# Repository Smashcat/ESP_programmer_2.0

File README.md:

# ESP_programmer_2.0
A USB to serial device plus circuit to automatically put ESP8266 and ESP32 modules into programming mode when programming via Arduino. Board is based around the CP2104 USB to serial bridge. All parts surface mount, except for header pins - project created using Eagle.

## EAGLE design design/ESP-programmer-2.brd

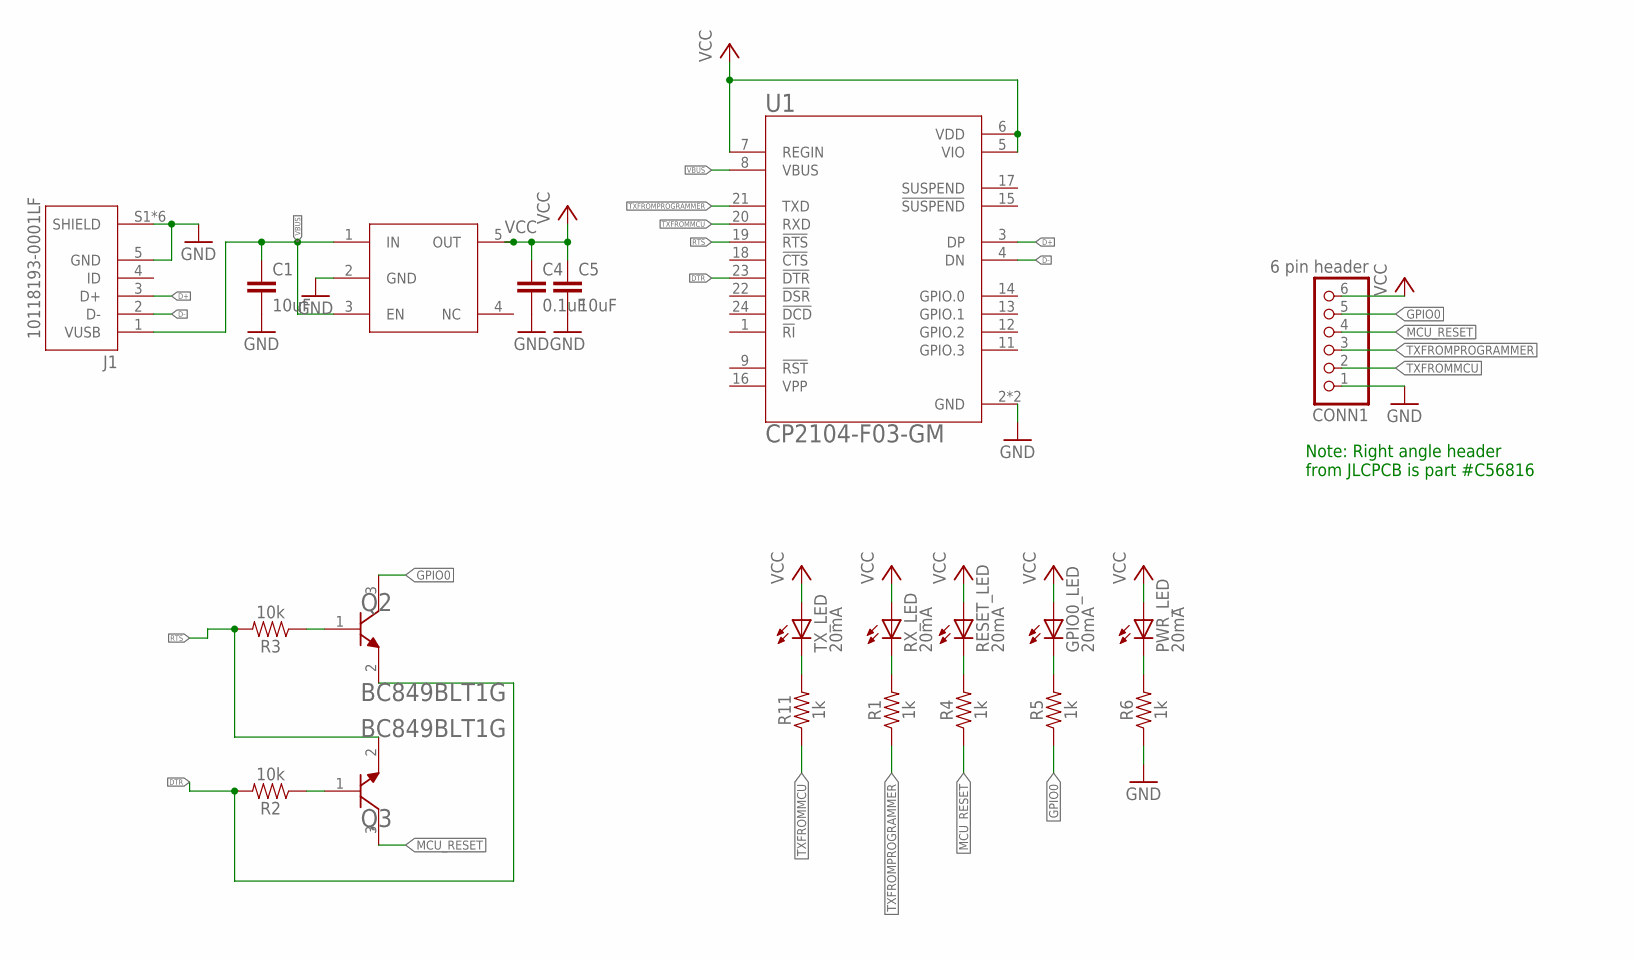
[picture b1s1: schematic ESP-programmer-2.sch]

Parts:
C1, C5: 10uF; C0603
C4: 0.1uF; C0603
CONN1: 6 pin header; 1X06
GPIO0_LED: 20mA; CHIP-LED0603
J1: 10118193-0001LF; FCI_10118193-0001LF
PWR_LED: 20mA; CHIP-LED0603
Q2, Q3: ON_SEMICONDUCTOR_BC849BLT1GON_SEMICONDUCTOR_BC849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; ON_SEMICONDUCTOR_BC849BLT1G_0
R1, R4, R5, R6, R11: 1k; 0603
R2, R3: 10k; 0603
REG: 3v3 LDO; NCP718BSN330T1G
RESET_LED: 20mA; CHIP-LED0603
RX_LED: 20mA; CHIP-LED0603
TX_LED: 20mA; CHIP-LED0603
U1: CP2104-F03-GM; QFN50P400X400X80-25N

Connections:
D+: J1.3 (D+), U1.3 (DP)
D-: J1.2 (D-), U1.4 (DN)
DTR: Q2.2 (E), R2.2, U1.23 (!DTR)
GND: C1.2, C4.2, C5.2, CONN1.1, J1.5 (GND), J1.S1 (SHIELD), J1.S2 (SHIELD), J1.S3 (SHIELD), J1.S4 (SHIELD), J1.S5 (SHIELD), J1.S6 (SHIELD), R6.1, REG.2 (GND), U1.2 (GND), U1.25 (GND)
GPIO0: CONN1.5, Q2.3 (C), R5.1
MCU_RESET: CONN1.4, Q3.3 (C), R4.1
unnamed: Q3.1 (B), R2.1
unnamed: Q2.1 (B), R3.1
RTS: Q3.2 (E), R3.2, U1.19 (!RTS)
STATUSTOLED: R11.2, TX_LED.C
STATUSTOLED1: R1.2, RX_LED.C
STATUSTOLED2: R4.2, RESET_LED.C
STATUSTOLED3: GPIO0_LED.C, R5.2
STATUSTOLED4: PWR_LED.C, R6.2
TXFROMMCU: CONN1.2, R11.1, U1.20 (RXD)
TXFROMPROGRAMMER: CONN1.3, R1.1, U1.21 (TXD)
VBUS: C1.1, J1.1 (VUSB), REG.1 (IN), REG.3 (EN), U1.8 (VBUS)
VCC: C4.1, C5.1, CONN1.6, GPIO0_LED.A, PWR_LED.A, REG.5 (OUT), RESET_LED.A, RX_LED.A, TX_LED.A, U1.5 (VIO), U1.6 (VDD), U1.7 (REGIN)

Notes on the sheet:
Note: Right angle header from JLCPCB is part #C56816

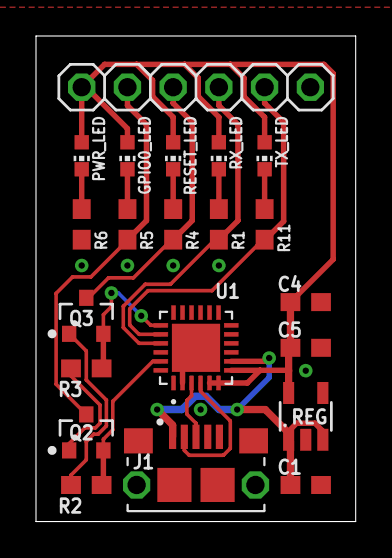
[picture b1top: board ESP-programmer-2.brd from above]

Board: 2 copper layers, 17.8 x 27.0 mm, 21 parts (0 on the bottom side), 18 nets.

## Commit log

2022-01-17 Added production and assembly files
2023-10-25 Fixed errors in mount file

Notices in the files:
parts and their libraries:
SparkFun-Resistors: Licensing: Creative Commons ShareAlike 4.0 International - https://creativecommons.org/licenses/by-sa/4.0
